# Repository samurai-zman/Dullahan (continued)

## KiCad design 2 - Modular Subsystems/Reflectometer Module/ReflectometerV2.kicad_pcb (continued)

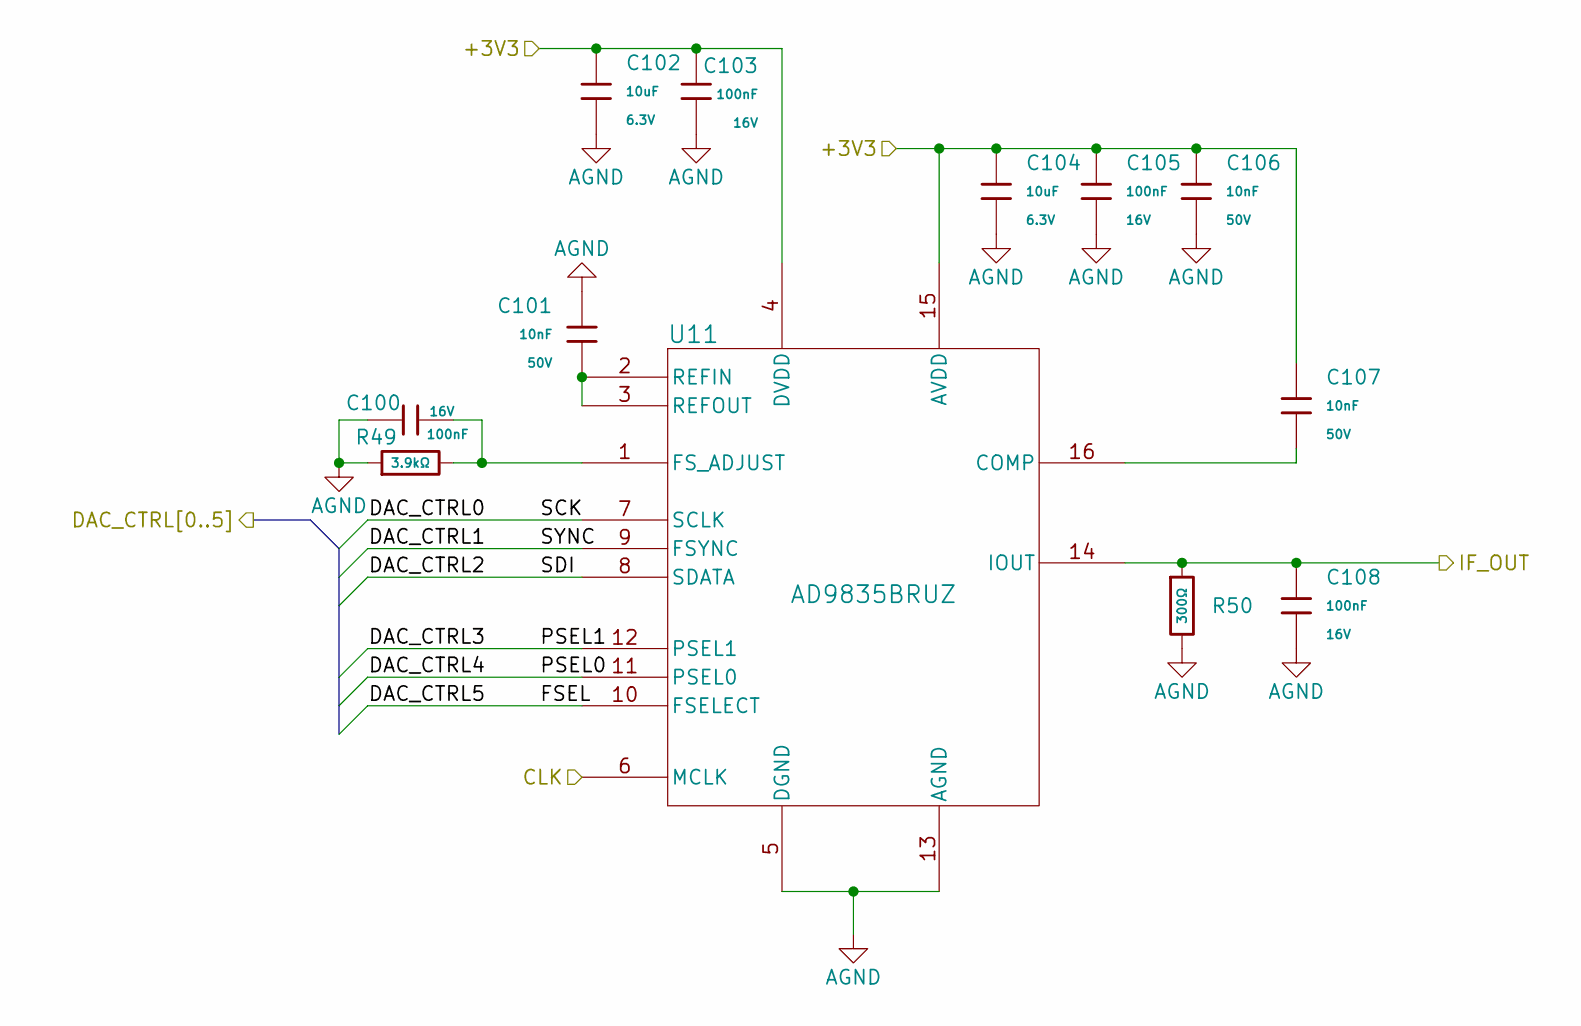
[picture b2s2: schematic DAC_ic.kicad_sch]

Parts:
C100, C103, C105, C108: 100nF; C_0402; Voltage Rated 16V; Tolerance ±10%; Part CL05B104KO5NNNC; LCSC C1525
C101, C106, C107: 10nF; C_0402; Voltage Rated 50V; Tolerance ±10%; Part CL05B103KB5NNNC; LCSC C15195
C102, C104: 10uF; C_0402; Voltage Rated 6.3V; Tolerance ±20%; Part CL05A106MQ5NUNC; LCSC C15525
R49: 3.9kΩ; R_0402; Overload Voltage (Max) 50V; Tolerance ±1%; Part 0402WGF3901TCE; LCSC C51721
R50: 300Ω; R_0402; Overload Voltage (Max) 50V; Tolerance ±1%; Part 0402WGF3000TCE; LCSC C25102
U11: AD9835BRUZ; RU_16_ADI

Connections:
/Clock/CLK_DAC: U11.6 (MCLK); also elsewhere on the board
/DAC/DAC_CTRL0: U11.7 (SCLK); also elsewhere on the board
/DAC/DAC_CTRL1: U11.9 (FSYNC); also elsewhere on the board
/DAC/DAC_CTRL2: U11.8 (SDATA); also elsewhere on the board
/DAC/DAC_CTRL3: U11.12 (PSEL1); also elsewhere on the board
/DAC/DAC_CTRL4: U11.11 (PSEL0); also elsewhere on the board
/DAC/DAC_CTRL5: U11.10 (FSELECT); also elsewhere on the board
/DAC/IF_OUT: C108.1, R50.1, U11.14 (IOUT); also elsewhere on the board
AGND: C100.1, C101.2, C102.2, C103.2, C104.2, C105.2, C106.1, C108.2, R49.1, R50.2, U11.5 (DGND), U11.13 (AGND); also elsewhere on the board
unnamed: C107.1, U11.16 (COMP)
unnamed: C100.2, R49.2, U11.1 (FS_ADJUST)
unnamed: C101.1, U11.2 (REFIN), U11.3 (REFOUT)

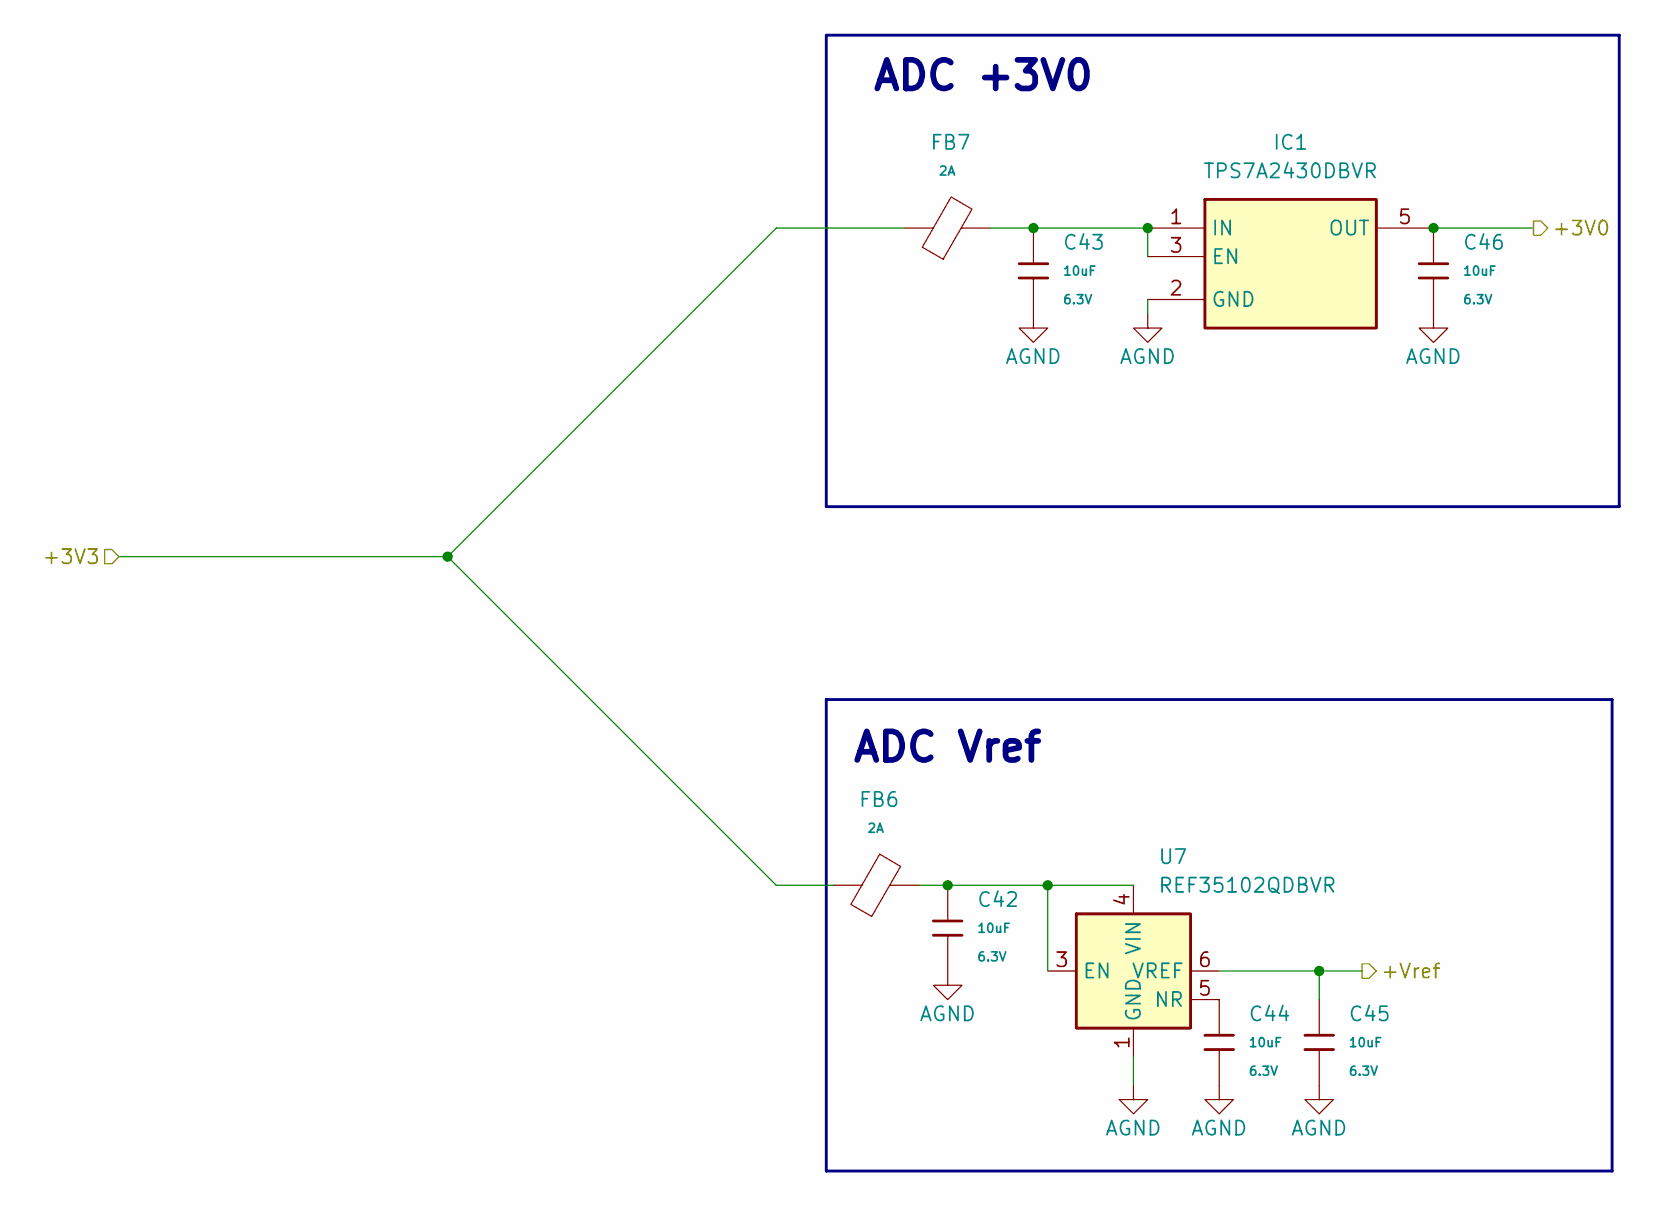
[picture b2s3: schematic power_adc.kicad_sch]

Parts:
C42, C43, C44, C45, C46: 10uF; C_0402; Voltage Rated 6.3V; Tolerance ±20%; Part CL05A106MQ5NUNC; LCSC C15525
FB6, FB7: FB_0603; Current Rating 2A; Tolerance ±25%; Part BLM18PG121SN1D; LCSC C14709
IC1: TPS7A2430DBVR; SOT95P280X145-5N; Mouser Part Number 595-TPS7A2430DBVR
U7: REF35102QDBVR; SOT-23-6

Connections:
/ADC Supply/+3V0: C46.1, IC1.5 (OUT); also elsewhere on the board
/ADC Supply/+Vref: C45.1, U7.6 (VREF); also elsewhere on the board
AGND: C42.2, C43.2, C44.2, C45.2, C46.2, IC1.2 (GND), U7.1 (GND), U7.2 (GND); also elsewhere on the board
unnamed: C43.1, FB7.2, IC1.1 (IN), IC1.3 (EN)
unnamed: C42.1, FB6.2, U7.3 (EN), U7.4 (VIN)
unnamed: C44.1, U7.5 (NR)

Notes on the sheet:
ADC Vref
ADC +3V0

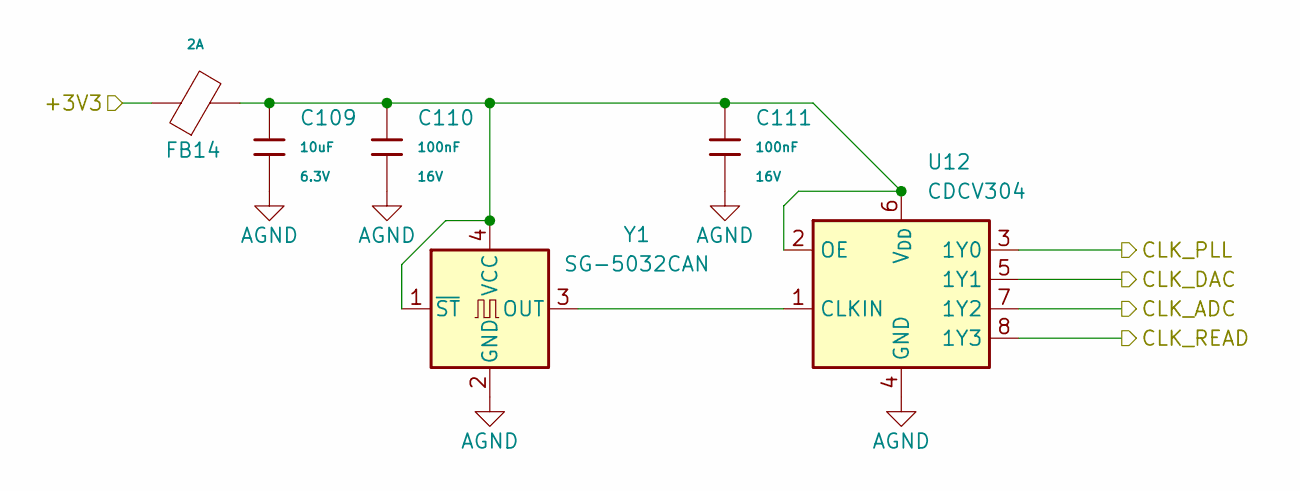
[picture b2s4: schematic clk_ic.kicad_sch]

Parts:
C109: 10uF; C_0402; Voltage Rated 6.3V; Tolerance ±20%; Part CL05A106MQ5NUNC; LCSC C15525
C110, C111: 100nF; C_0402; Voltage Rated 16V; Tolerance ±10%; Part CL05B104KO5NNNC; LCSC C1525
FB14: FB_0603; Current Rating 2A; Tolerance ±25%; Part BLM18PG121SN1D; LCSC C14709
U12: CDCV304; TSSOP-8_4.4x3mm_P0.65mm
Y1: SG-5032CAN; Oscillator_SMD_SeikoEpson_SG8002LB-4Pin_5.0x3.2mm

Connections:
/ADC/CLK: U12.7 (1Y2); also elsewhere on the board
/Clock/CLK_DAC: U12.5 (1Y1); also elsewhere on the board
/Clock/CLK_PLL: U12.3 (1Y0); also elsewhere on the board
/Clock/CLK_READ: U12.8 (1Y3); also elsewhere on the board
AGND: C109.2, C110.2, C111.2, U12.4 (GND), Y1.2 (GND); also elsewhere on the board
unnamed: U12.1 (CLKIN), Y1.3 (OUT)
unnamed: C109.1, C110.1, C111.1, FB14.2, U12.2 (OE), U12.6 (V_{DD}), Y1.1 (~ST), Y1.4 (VCC)

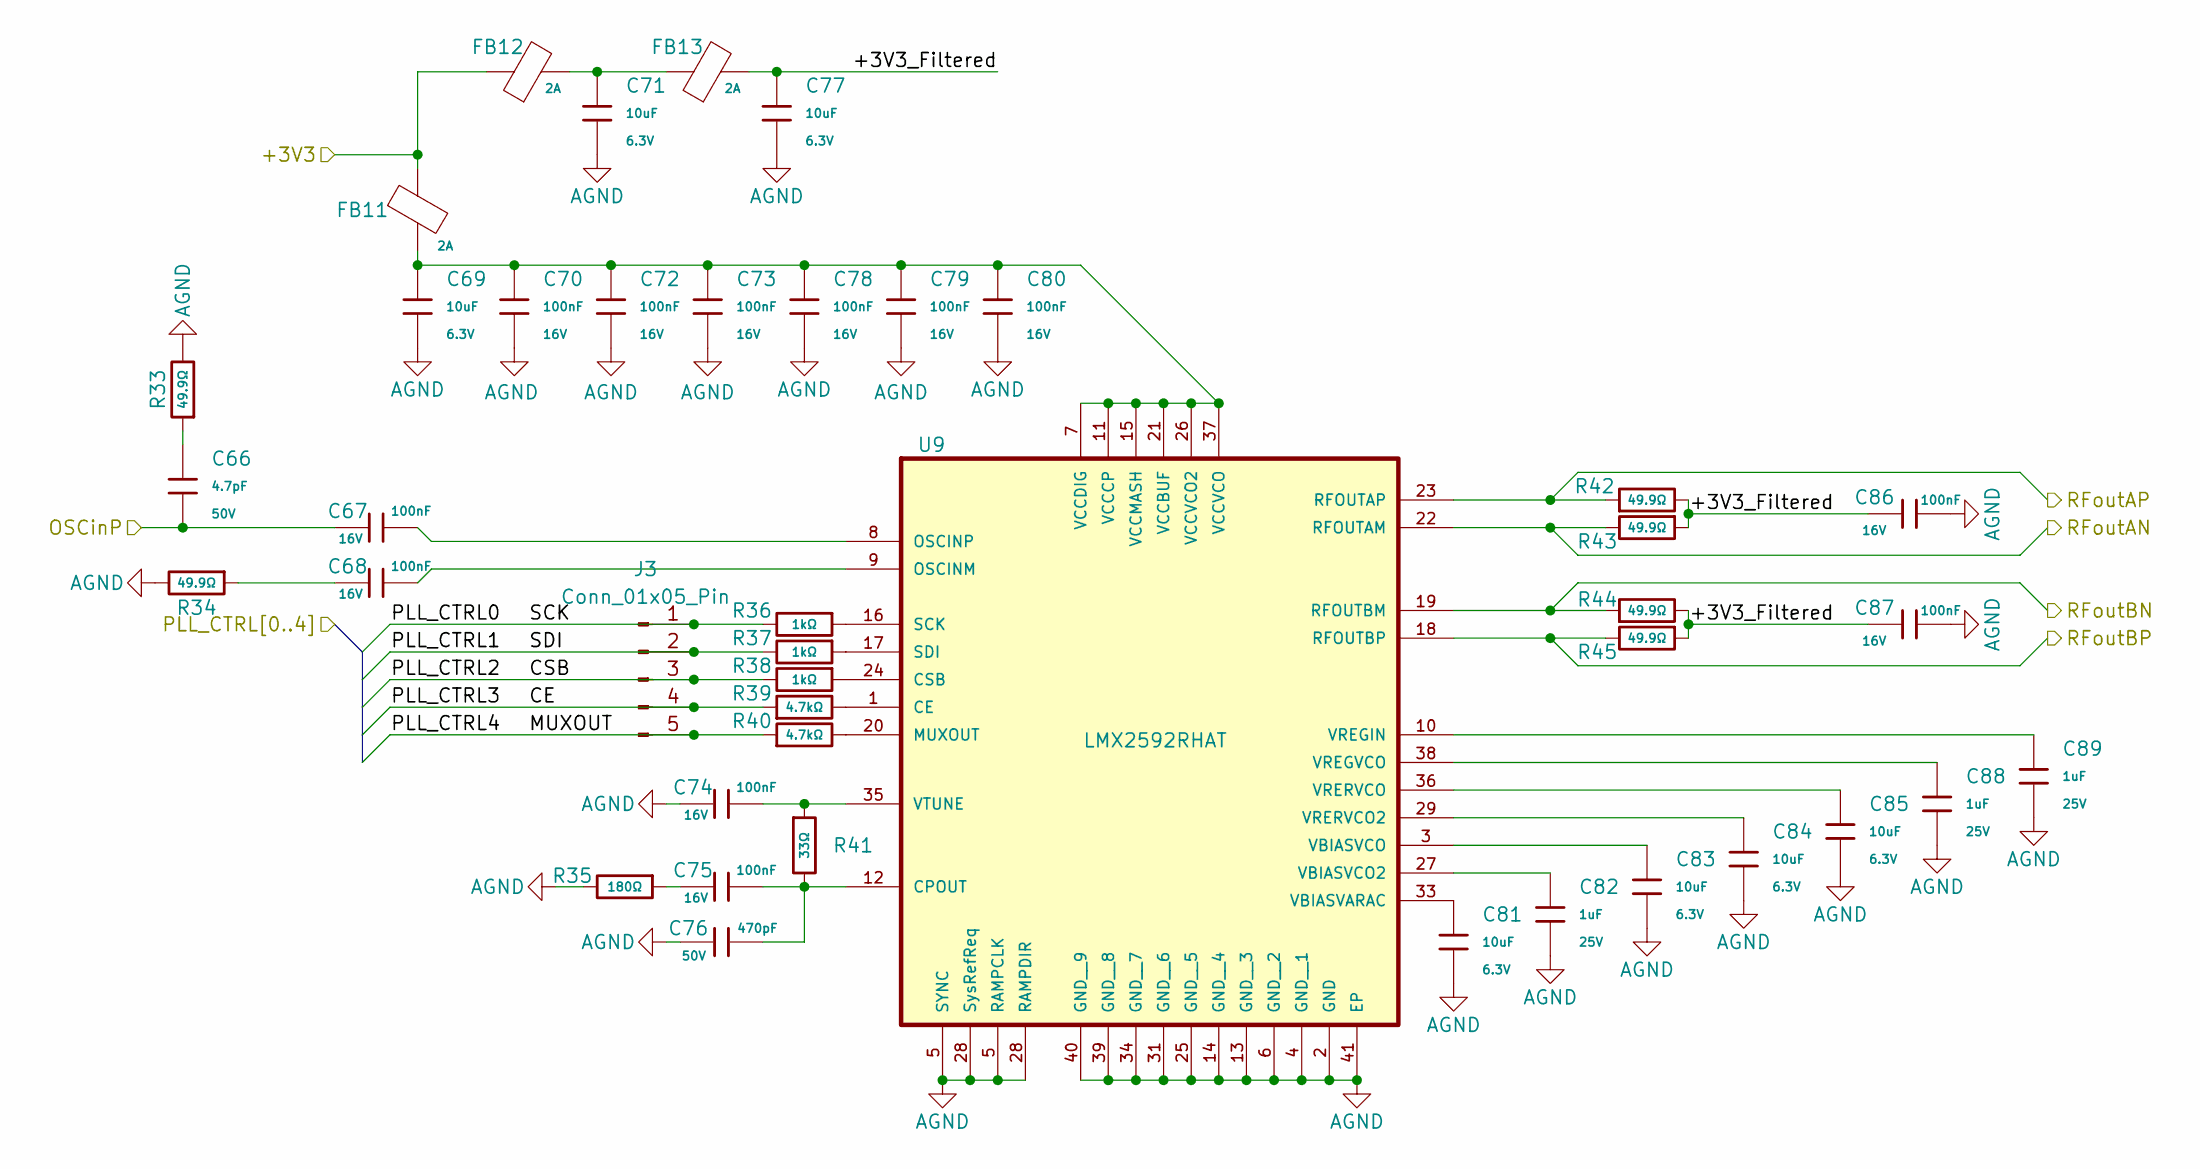
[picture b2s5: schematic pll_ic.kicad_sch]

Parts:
C66: 4.7pF; C_0402; Voltage Rated 50V; Part 0402CG4R7C500NT; LCSC C1569
C67, C68, C70, C72, C73, C74, C75, C78, C79, C80, C86, C87: 100nF; C_0402; Voltage Rated 16V; Tolerance ±10%; Part CL05B104KO5NNNC; LCSC C1525
C69, C71, C77, C81, C83, C84, C85: 10uF; C_0402; Voltage Rated 6.3V; Tolerance ±20%; Part CL05A106MQ5NUNC; LCSC C15525
C76: 470pF; C_0402; Voltage Rated 50V; Tolerance ±10%; Part 0402B471K500NT; LCSC C1537
C82, C88, C89: 1uF; C_0402; Voltage Rated 25V; Tolerance ±10%; Part CL05A105KA5NQNC; LCSC C52923
FB11, FB12, FB13: FB_0603; Current Rating 2A; Tolerance ±25%; Part BLM18PG121SN1D; LCSC C14709
J3: Conn_01x05_Pin; PinHeader_1x05_P2.54mm_Vertical
R33, R34, R42, R43, R44, R45: 49.9Ω; R_0402; Overload Voltage (Max) 50V; Tolerance ±1%; Part 0402WGF499JTCE; LCSC C25120
R35: 180Ω; R_0402; Overload Voltage (Max) 50V; Tolerance ±1%; Part 0402WGF1001TCE; LCSC C11702
R36, R37, R38: 1kΩ; R_0402; Overload Voltage (Max) 50V; Tolerance ±1%; Part 0402WGF1001TCE; LCSC C11702
R39, R40: 4.7kΩ; R_0402; Overload Voltage (Max) 50V; Tolerance ±1%; Part 0402WGF4701TCE; LCSC C25900
R41: 33Ω; R_0402; Overload Voltage (Max) 50V; Tolerance ±1%; Part 0402WGF330JTCE; LCSC C25105
U9: LMX2592RHAT; QFN50P600X600X100-41N

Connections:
/Clock/CLK_PLL: C66.2, C67.2; also elsewhere on the board
/DAC/DAC_CTRL0: J3.1, R36.2; also elsewhere on the board
/DAC/DAC_CTRL2: J3.2, R37.2; also elsewhere on the board
/DOWNMIXER/LON: R44.1, U9.19 (RFOUTBM); also elsewhere on the board
/DOWNMIXER/LOP: R45.2, U9.18 (RFOUTBP); also elsewhere on the board
/M2 Connector/PLL_CTRL2: J3.3, R38.2; also elsewhere on the board
/M2 Connector/PLL_CTRL3: J3.4, R39.1; also elsewhere on the board
/M2 Connector/PLL_CTRL4: J3.5, R40.1; also elsewhere on the board
/PLL/+3V3_Filtered: C77.1, C86.1, C87.1, FB13.2, R42.2, R43.1, R44.2, R45.1
/PLL/RFoutAN: R43.2, U9.22 (RFOUTAM); also elsewhere on the board
/PLL/RFoutAP: R42.1, U9.23 (RFOUTAP); also elsewhere on the board
AGND: C69.2, C70.2, C71.2, C72.2, C73.2, C74.2, C76.1, C77.2, C78.2, C79.2, C80.2, C81.2, C82.2, C83.2, C84.2, C85.2, C86.2, C87.2, C88.2, C89.2, R33.2, R34.2, R35.2, U9.2 (GND), U9.4 (GND__1), U9.5 (SYNC), U9.6 (GND__2), U9.13 (GND__3), U9.14 (GND__4), U9.25 (GND__5), U9.28 (RAMPDIR), U9.31 (GND__6), U9.34 (GND__7), U9.39 (GND__8), U9.40 (GND__9), U9.41 (EP); also elsewhere on the board
unnamed: C66.1, R33.1
unnamed: C68.2, R34.1
unnamed: C71.1, FB12.2, FB13.1
unnamed: C75.2, R35.1
unnamed: R39.2, U9.1 (CE)
unnamed: C75.1, C76.2, R41.2, U9.12 (CPOUT)
unnamed: R38.1, U9.24 (CSB)
unnamed: R40.2, U9.20 (MUXOUT)
unnamed: C68.1, U9.9 (OSCINM)
unnamed: C67.1, U9.8 (OSCINP)
unnamed: R36.1, U9.16 (SCK)
unnamed: R37.1, U9.17 (SDI)
unnamed: C81.1, U9.33 (VBIASVARAC)
unnamed: C82.1, U9.27 (VBIASVCO2)
unnamed: C83.1, U9.3 (VBIASVCO)
unnamed: C69.1, C70.1, C72.1, C73.1, C78.1, C79.1, C80.1, FB11.2, U9.7 (VCCDIG), U9.11 (VCCCP), U9.15 (VCCMASH), U9.21 (VCCBUF), U9.26 (VCCVCO2), U9.37 (VCCVCO)
unnamed: C89.1, U9.10 (VREGIN)
unnamed: C88.1, U9.38 (VREGVCO)
unnamed: C84.1, U9.29 (VRERVCO2)
unnamed: C85.1, U9.36 (VRERVCO)
unnamed: C74.1, R41.1, U9.35 (VTUNE)

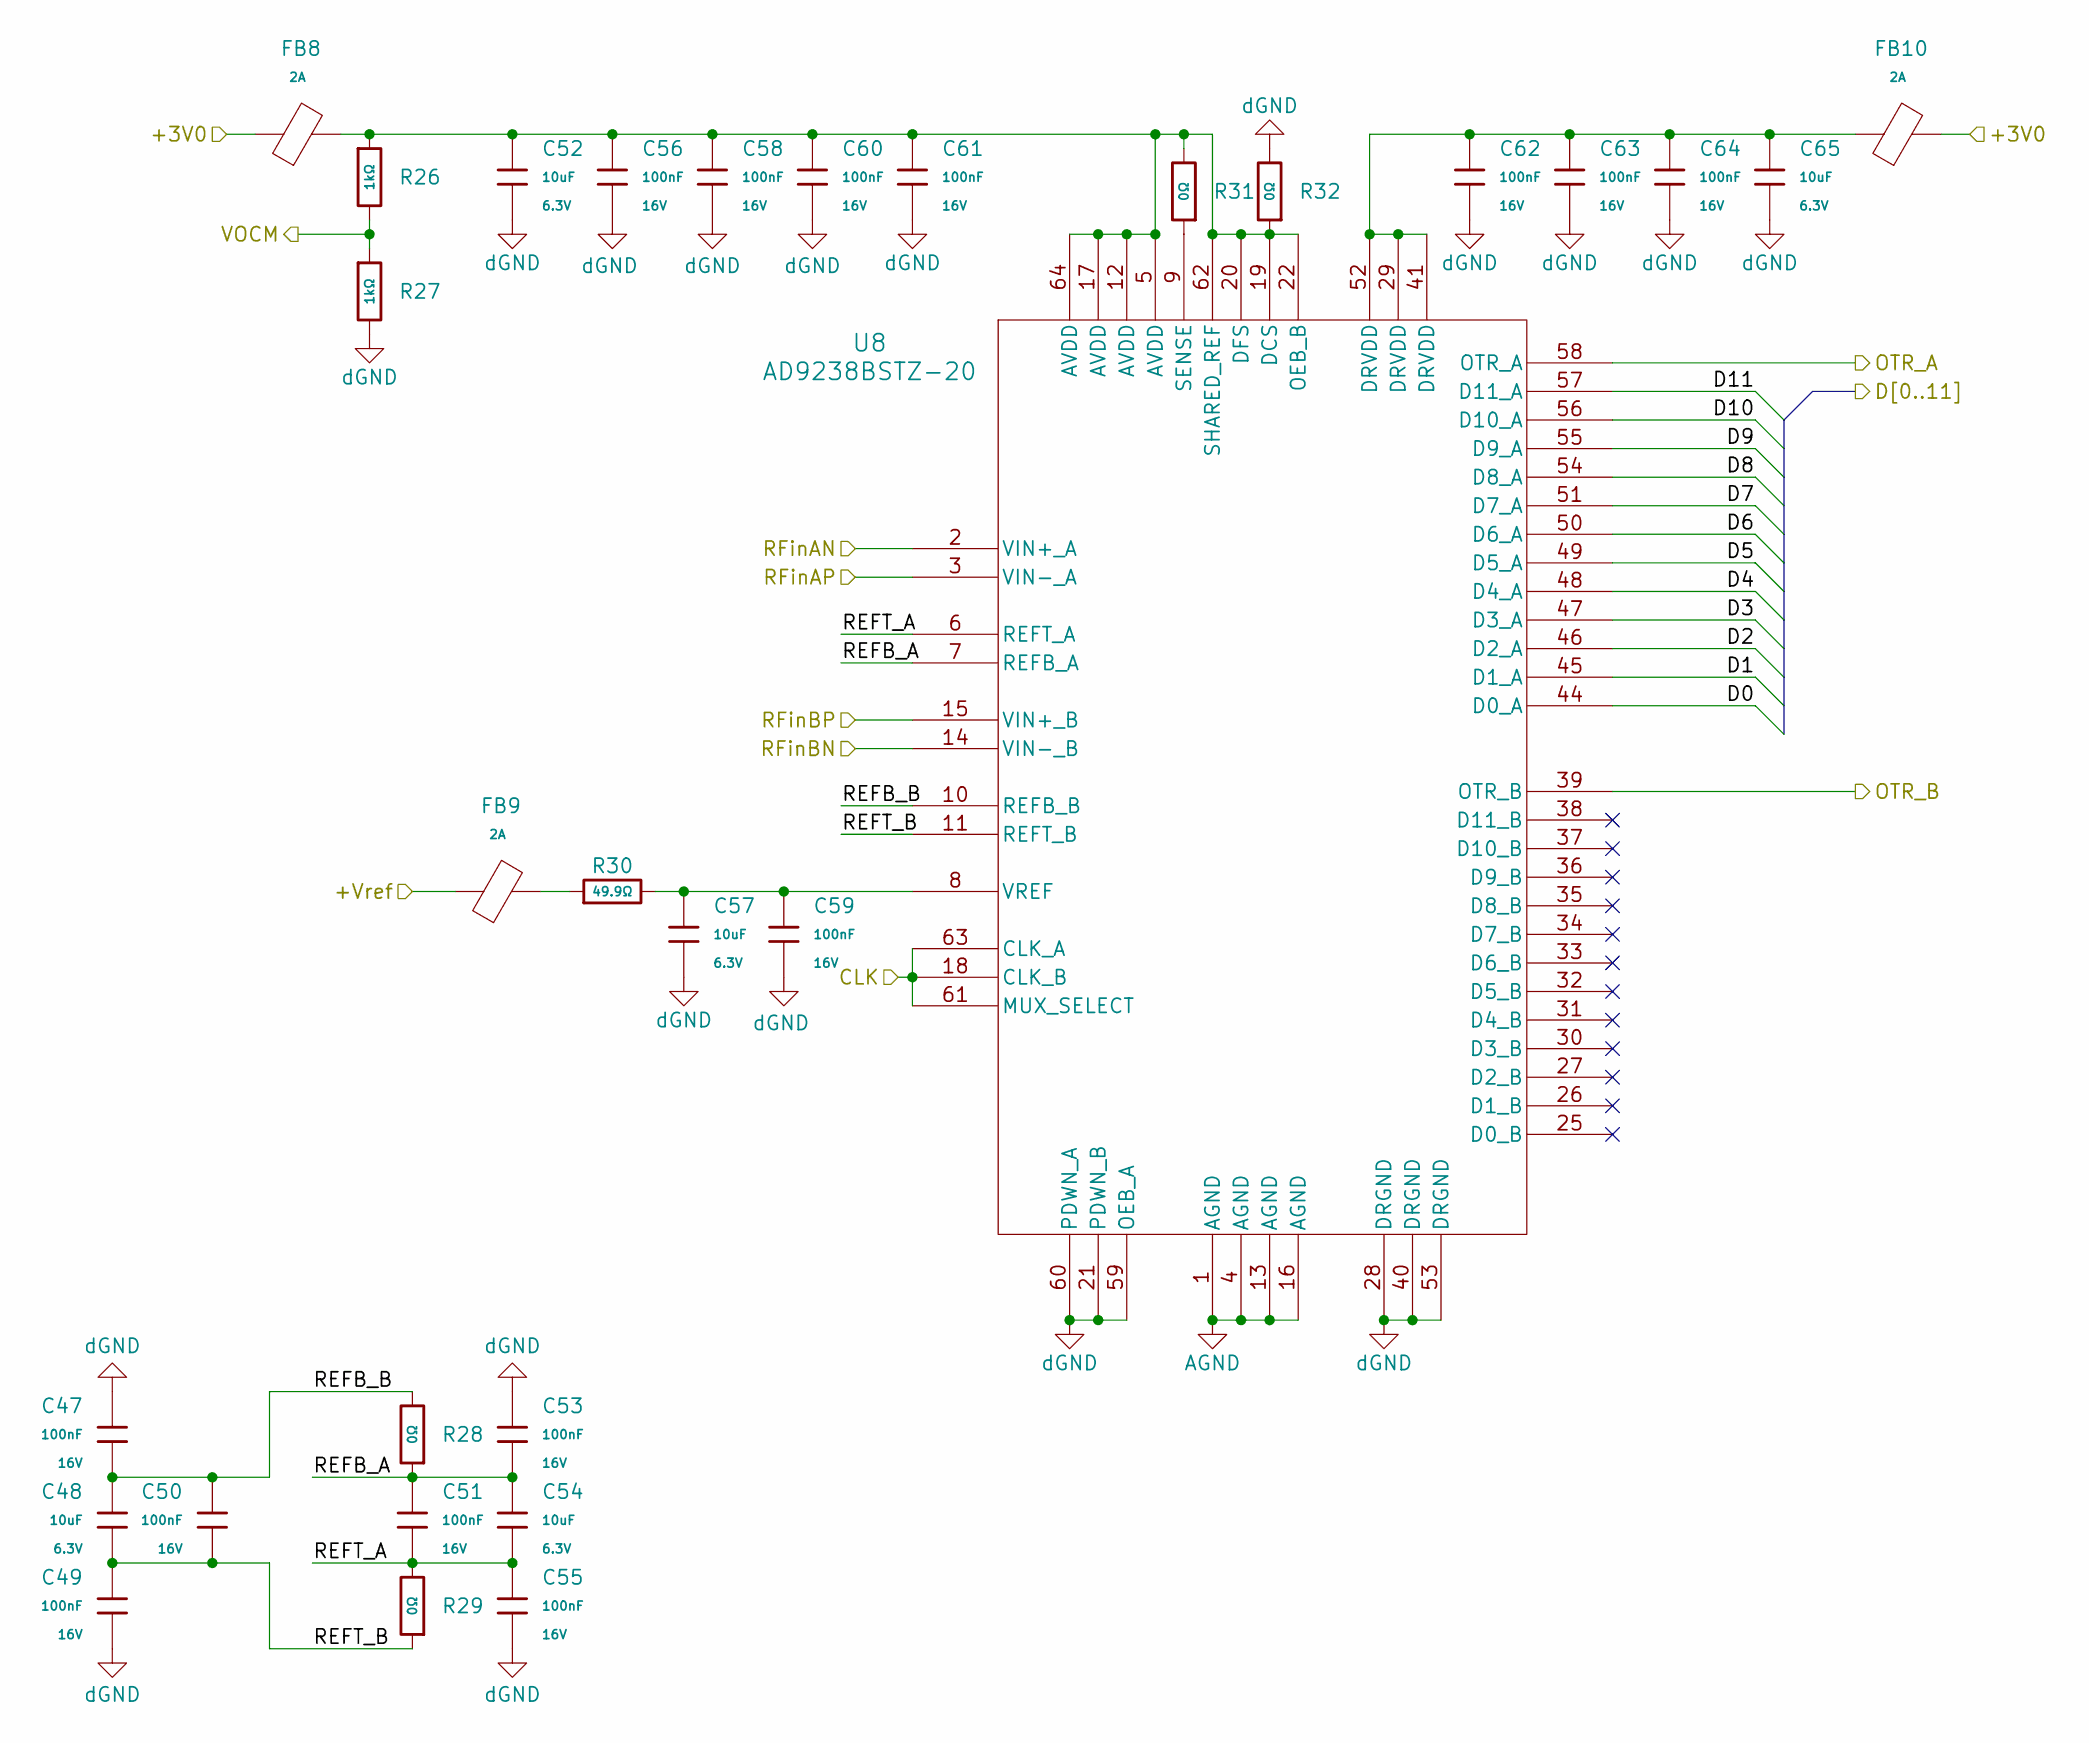
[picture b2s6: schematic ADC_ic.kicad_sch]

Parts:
C47, C49, C50, C51, C53, C55, C56, C58, C59, C60, C61, C62, C63, C64: 100nF; C_0402; Voltage Rated 16V; Tolerance ±10%; Part CL05B104KO5NNNC; LCSC C1525
C48, C52, C54, C57, C65: 10uF; C_0402; Voltage Rated 6.3V; Tolerance ±20%; Part CL05A106MQ5NUNC; LCSC C15525
FB8, FB9, FB10: FB_0603; Current Rating 2A; Tolerance ±25%; Part BLM18PG121SN1D; LCSC C14709
R26, R27: 1kΩ; R_0402; Overload Voltage (Max) 50V; Tolerance ±1%; Part 0402WGF1001TCE; LCSC C11702
R28, R29, R31, R32: 0Ω; R_0402; Overload Voltage (Max) 50V; Tolerance ±1%; Part 0402WGF0000TCE; LCSC C17168
R30: 49.9Ω; R_0402; Overload Voltage (Max) 50V; Tolerance ±1%; Part 0402WGF499JTCE; LCSC C25120
U8: AD9238BSTZ-20; ST_64_1_ADI

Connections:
/ADC Supply/+3V0: FB8.1, FB10.2; also elsewhere on the board
/ADC Supply/+Vref: FB9.1; also elsewhere on the board
/ADC/CLK: U8.18 (CLK_B), U8.61 (MUX_SELECT), U8.63 (CLK_A); also elsewhere on the board
/ADC/D0: U8.44 (D0_A); also elsewhere on the board
/ADC/D1: U8.45 (D1_A); also elsewhere on the board
/ADC/D2: U8.46 (D2_A); also elsewhere on the board
/ADC/D3: U8.47 (D3_A); also elsewhere on the board
/ADC/D4: U8.48 (D4_A); also elsewhere on the board
/ADC/D5: U8.49 (D5_A); also elsewhere on the board
/ADC/D6: U8.50 (D6_A); also elsewhere on the board
/ADC/D7: U8.51 (D7_A); also elsewhere on the board
/ADC/D8: U8.54 (D8_A); also elsewhere on the board
/ADC/D9: U8.55 (D9_A); also elsewhere on the board
/ADC/D10: U8.56 (D10_A); also elsewhere on the board
/ADC/D11: U8.57 (D11_A); also elsewhere on the board
/ADC/OTR_A: U8.58 (OTR_A); also elsewhere on the board
/ADC/OTR_B: U8.39 (OTR_B); also elsewhere on the board
/ADC/REFB_A: C51.1, C53.2, C54.1, R28.1, U8.7 (REFB_A)
/ADC/REFB_B: C47.2, C48.1, C50.1, R28.2, U8.10 (REFB_B)
/ADC/REFT_A: C51.2, C54.2, C55.1, R29.2, U8.6 (REFT_A)
/ADC/REFT_B: C48.2, C49.1, C50.2, R29.1, U8.11 (REFT_B)
/ADC/RFinAN: U8.2 (VIN+_A); also elsewhere on the board
/ADC/RFinAP: U8.3 (VIN-_A); also elsewhere on the board
/ADC/RFinBN: U8.14 (VIN-_B); also elsewhere on the board
/ADC/RFinBP: U8.15 (VIN+_B); also elsewhere on the board
/ADC/VOCM: R26.2, R27.1; also elsewhere on the board
AGND: C47.1, C49.2, C52.2, C53.1, C55.2, C56.2, C57.2, C58.2, C59.2, C60.2, C61.2, C62.2, C63.2, C64.2, C65.2, R27.2, R32.2, U8.1 (AGND), U8.4 (AGND), U8.13 (AGND), U8.16 (AGND), U8.21 (PDWN_B), U8.28 (DRGND), U8.40 (DRGND), U8.53 (DRGND), U8.59 (OEB_A), U8.60 (PDWN_A); also elsewhere on the board
unnamed: C62.1, C63.1, C64.1, C65.1, FB10.1, U8.29 (DRVDD), U8.41 (DRVDD), U8.52 (DRVDD)
unnamed: FB9.2, R30.1
unnamed: C52.1, C56.1, C58.1, C60.1, C61.1, FB8.2, R26.1, R31.2, R32.1, U8.5 (AVDD), U8.12 (AVDD), U8.17 (AVDD), U8.19 (DCS), U8.20 (DFS), U8.22 (OEB_B), U8.62 (SHARED_REF), U8.64 (AVDD)
unnamed: R31.1, U8.9 (SENSE)
unnamed: C57.1, C59.1, R30.2, U8.8 (VREF)

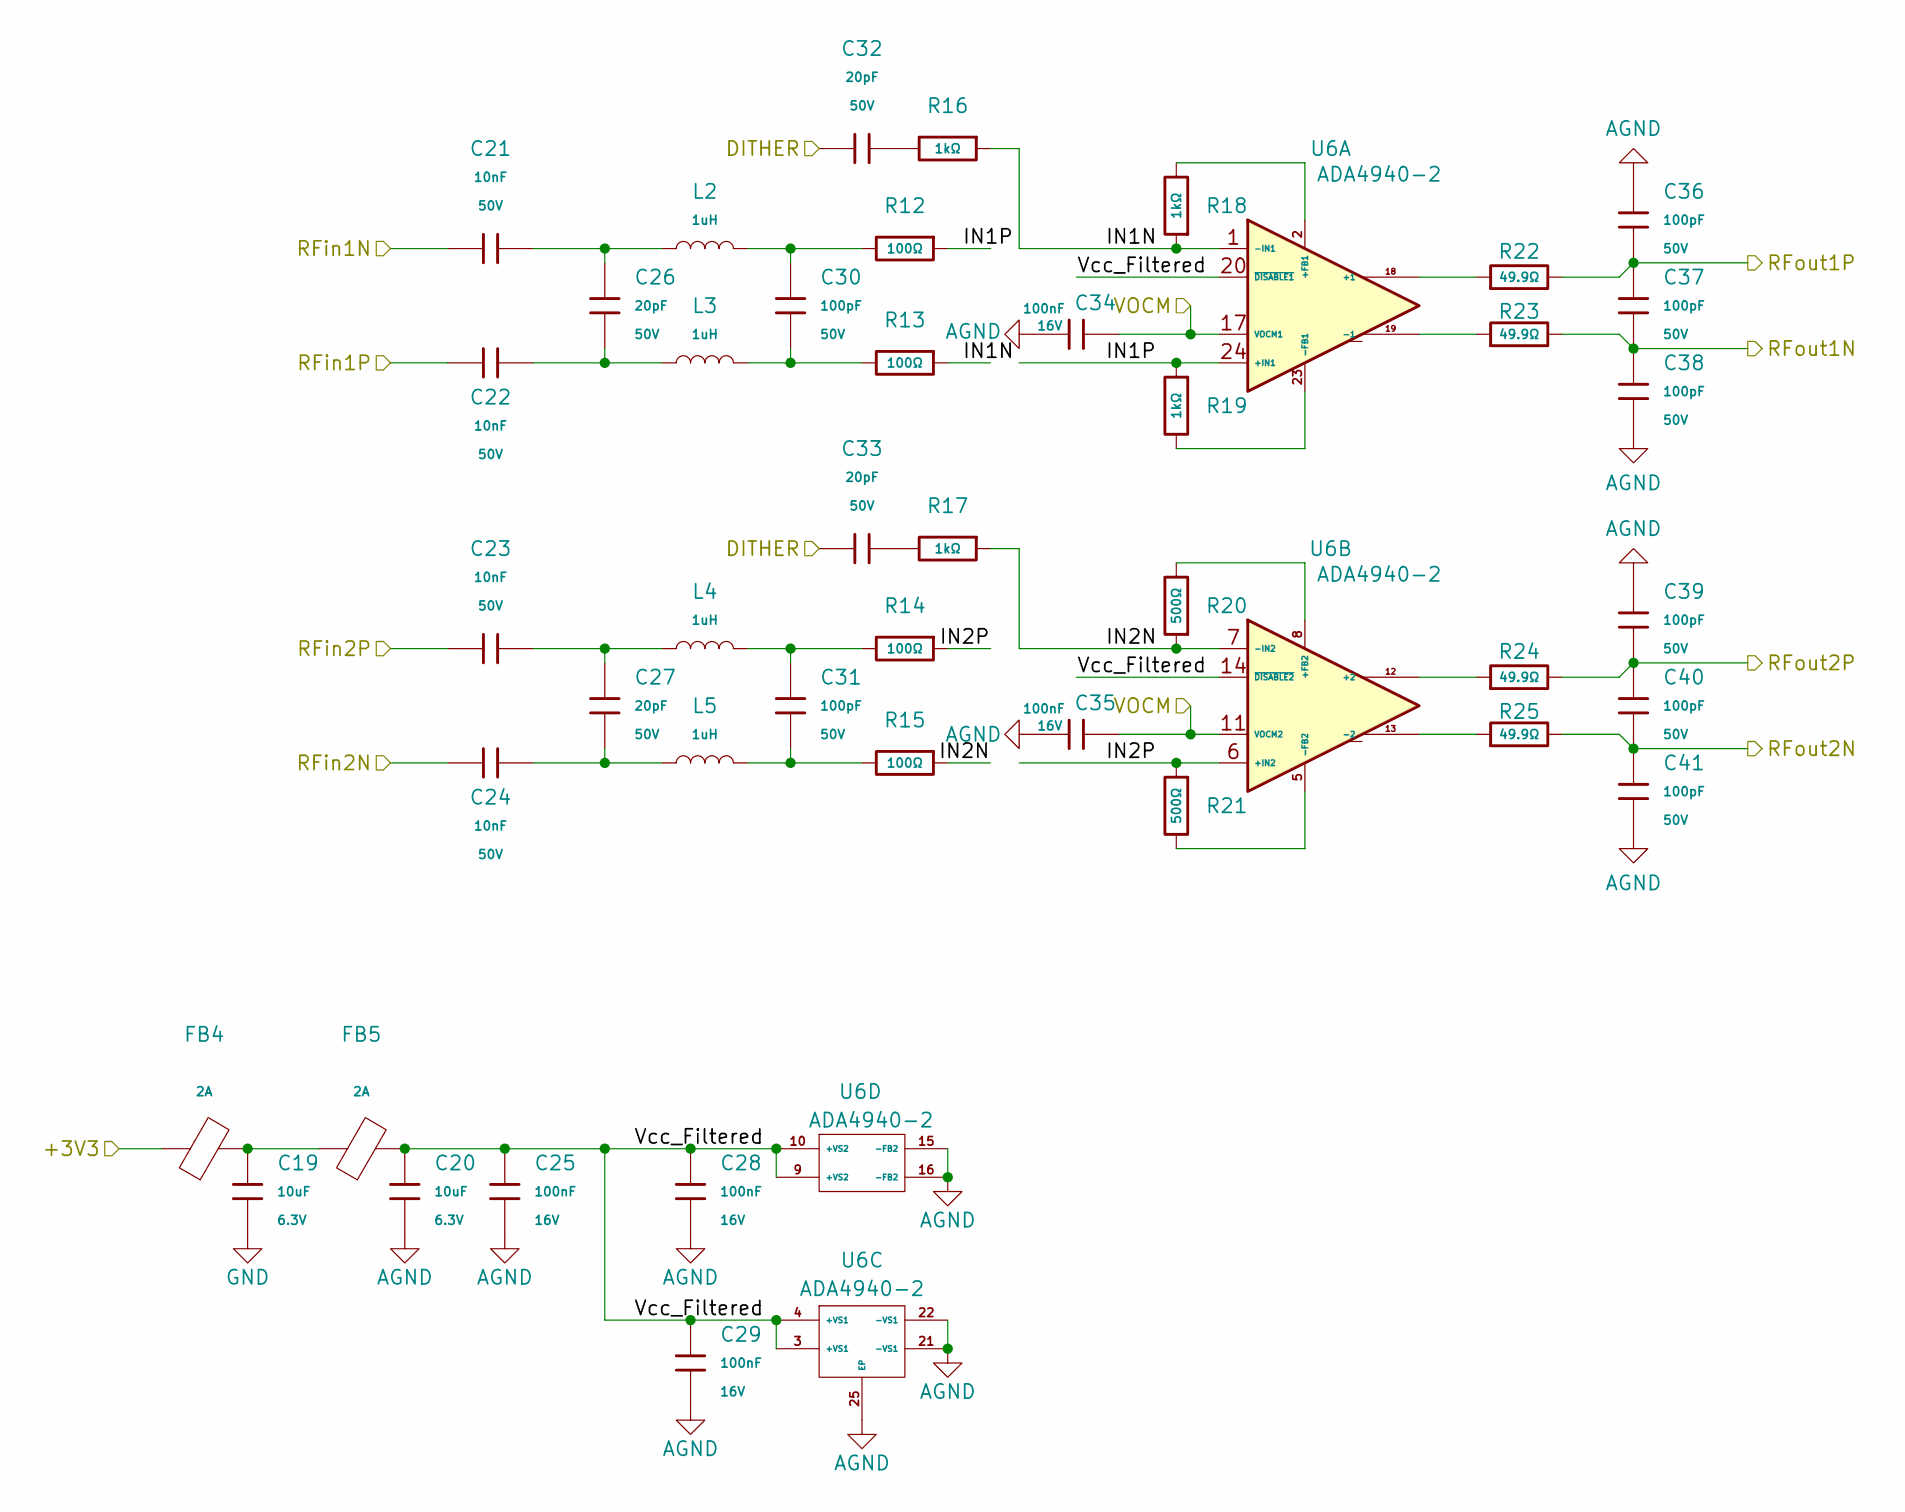
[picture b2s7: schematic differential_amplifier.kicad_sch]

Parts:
C19, C20: 10uF; C_0402; Voltage Rated 6.3V; Tolerance ±20%; Part CL05A106MQ5NUNC; LCSC C15525
C21, C22, C23, C24: 10nF; C_0402; Voltage Rated 50V; Tolerance ±10%; Part CL05B103KB5NNNC; LCSC C15195
C25, C28, C29, C34, C35: 100nF; C_0402; Voltage Rated 16V; Tolerance ±10%; Part CL05B104KO5NNNC; LCSC C1525
C26, C27, C32, C33: 20pF; C_0402; Voltage Rated 50V; Tolerance ±5%; Part 0402CG200J500NT; LCSC C1554
C30, C31, C36, C37, C38, C39, C40, C41: 100pF; C_0402; Voltage Rated 50V; Tolerance ±5%; Part 0402CG101J500NT; LCSC C1546
FB4, FB5: FB_0603; Current Rating 2A; Tolerance ±25%; Part BLM18PG121SN1D; LCSC C14709
L2, L3, L4, L5: 1uH; L_0402; Part SDCL1005C3N9STDF; LCSC C14033
R12, R13, R14, R15: 100Ω; R_0402; Overload Voltage (Max) 50V; Tolerance ±1%; Part 0402WGF1001TCE; LCSC C11702
R16, R17, R18, R19: 1kΩ; R_0402; Overload Voltage (Max) 50V; Tolerance ±1%; Part 0402WGF1001TCE; LCSC C11702
R20, R21: 500Ω; R_0402; Overload Voltage (Max) 50V; Tolerance ±1%; Part 0402WGF1001TCE; LCSC C11702
R22, R23, R24, R25: 49.9Ω; R_0402; Overload Voltage (Max) 50V; Tolerance ±1%; Part 0402WGF499JTCE; LCSC C25120
U6: ADA4940-2; LFCSP-24-1EP_4x4mm_P0.5mm_EP2.5x2.5mm

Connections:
/ADC/RFinAN: C37.2, C38.1, R23.2; also elsewhere on the board
/ADC/RFinAP: C36.2, C37.1, R22.2; also elsewhere on the board
/ADC/RFinBN: C40.2, C41.1, R25.2; also elsewhere on the board
/ADC/RFinBP: C39.2, C40.1, R24.2; also elsewhere on the board
/ADC/VOCM: C34.1, C35.1, U6.11 (VOCM2), U6.17 (VOCM1); also elsewhere on the board
/DE Amplifier/DITHER: C32.1, C33.1; also elsewhere on the board
/DE Amplifier/IN1N: R13.1, R16.1, R18.1, U6.1 (-IN1)
/DE Amplifier/IN1P: R12.1, R19.1, U6.24 (+IN1)
/DE Amplifier/IN2N: R15.1, R17.1, R20.1, U6.7 (-IN2)
/DE Amplifier/IN2P: R14.1, R21.1, U6.6 (+IN2)
/DE Amplifier/RFin1N: C21.1; also elsewhere on the board
/DE Amplifier/RFin1P: C22.1; also elsewhere on the board
/DE Amplifier/RFin2N: C24.1; also elsewhere on the board
/DE Amplifier/RFin2P: C23.1; also elsewhere on the board
/DE Amplifier/Vcc_Filtered: C20.1, C25.1, C28.1, C29.1, FB5.2, U6.3 (+VS1), U6.4 (+VS1), U6.9 (+VS2), U6.10 (+VS2), U6.14 (~DISABLE2), U6.20 (~DISABLE1)
AGND: C19.1, C20.2, C25.2, C28.2, C29.2, C34.2, C35.2, C36.1, C38.2, C39.1, C41.2, U6.15 (-FB2), U6.16 (-FB2), U6.21 (-VS1), U6.22 (-VS1), U6.25 (EP); also elsewhere on the board
unnamed: C19.2, FB4.2, FB5.1
unnamed: C21.2, C26.2, L2.1
unnamed: C22.2, C26.1, L3.1
unnamed: C23.2, C27.2, L4.1
unnamed: C24.2, C27.1, L5.1
unnamed: C30.1, L2.2, R12.2
unnamed: C30.2, L3.2, R13.2
unnamed: C31.1, L4.2, R14.2
unnamed: C31.2, L5.2, R15.2
unnamed: C32.2, R16.2
unnamed: C33.2, R17.2
unnamed: R22.1, U6.18 (+1)
unnamed: R18.2, U6.2 (+FB1)
unnamed: R23.1, U6.19 (-1)
unnamed: R19.2, U6.23 (-FB1)
unnamed: R24.1, U6.12 (+2)
unnamed: R20.2, U6.8 (+FB2)
unnamed: R25.1, U6.13 (-2)
unnamed: R21.2, U6.5 (-FB2)
